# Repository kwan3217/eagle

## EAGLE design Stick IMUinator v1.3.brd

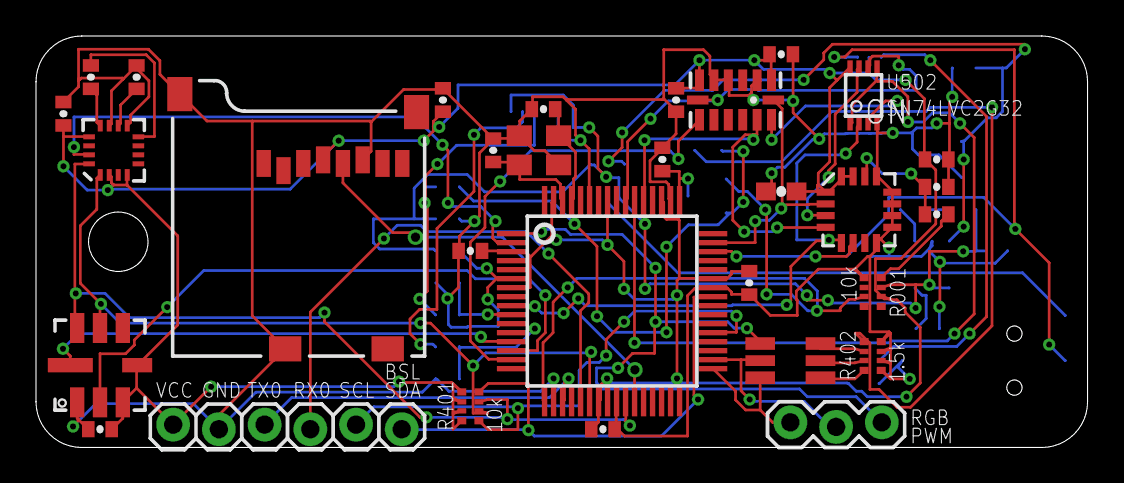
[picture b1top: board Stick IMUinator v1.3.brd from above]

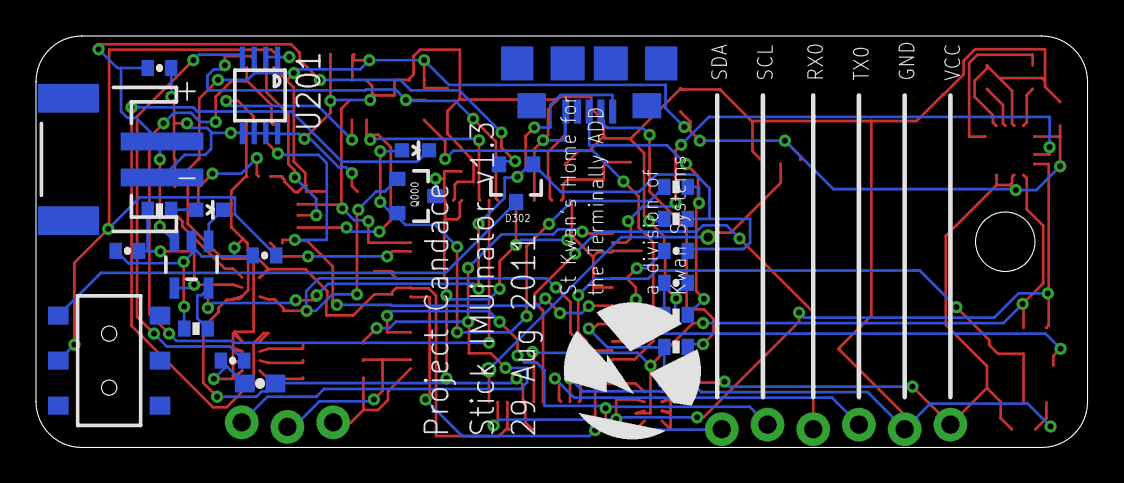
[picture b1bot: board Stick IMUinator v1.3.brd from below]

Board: 2 copper layers, 58.4 x 22.9 mm, 55 parts (23 on the bottom side), 53 nets.

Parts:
C010, C020, C461, C462: 22pF; 0402-CAP
C030, C101, C407, C423, C443, C451, C501, C601, C701, C802: 100nF; 0402-CAP
C201: 4.7uF; 0603-CAP
C203: 470pF; 0402-CAP
C204: 1uF; 0402-CAP
C301, C302, C606, C810: 4.7uF; 0402-CAP
C502: 10uF; 0603-CAP
C503: 10nF; 0402-CAP
C504: 470nF; 0402-CAP
C808: 220nF; 0402-CAP
D000, D301: RED; LED-0603
D302: PMEG2005CT; SOT-23-3
D401: GM5WA94310A
J301: JST 2mm; JST-2-SMD
J401: M06; 1X06_LOCK
J402: M03; 1X03_LOCK
JP1: STAND-OFF
Q000: PFET; SOT23-3
R001, R401: 10k; CRA04
R010, R020: 33; 0402-RES
R011, R302: 1.5k; 0402-RES
R031: 100k; 0402-RES
R301: 2.2k; 0402-RES
R402: 1.5k; CRA04
S201: SPST; AYZ0202
U101: BMP085
U201: 5219; MSOP08
U301: 73831; SOT23-5
U401: LPC2148; SQFP-S-10X10-64
U501: L3G4200D; LGA16-4X4
U502: SN74LVC2G32; DCU_8
U601: ADXL345; LGA14
U701: USD-SOCKETNEW; MICRO-SD-SOCKET-PP
U801: 5883; 16LPCC
U$1: USB_MICROB_JST; UB-MC5BR3-SD204-4S
Y401: TSX-3225; CRYSTAL_SMD

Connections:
ACCINT: U401.15, U601.8
AMOSI1: U502.3, U601.13
COMPINT: U401.2, U801.15
CONN_D+: R010.2, R011.2, U$1.3
CONN_D-: R020.2, U$1.2
CS0: U401.31, U701.2
CSA: U401.55, U502.6, U601.7
CSG: U401.9, U501.5, U502.2
EOC: U101.2, U401.14
GMOSI1: U501.3, U502.7
GND: C010.2, C020.2, C030.2, C101.2, C201.2, C203.2, C204.2, C301.2, C302.2, C407.2, C423.2, C443.2, C451.2, C461.1, C462.1, C501.2, C502.2, C503.2, C601.2, C606.2, C701.2, C802.2, C810.2, J301.1, J401.2, R001.1, R031.1, R301.1, R402.1, R402.2, R402.3, R402.4, U101.1, U201.5, U201.6, U201.7, U201.8, U301.2, U401.6, U401.18, U401.25, U401.42, U401.50, U401.59, U501.8, U501.9, U501.10, U501.11, U501.12, U501.13, U502.4, U601.2, U601.4, U601.5, U701.6, U701.CD2, U701.GND1, U801.9, U801.11, U$1.5, U$1.P$6, U$1.P$7, U$1.P$8, U$1.P$9, U$1.P$10, U$1.P$11, Y401.2, Y401.4
GYROINT: U401.46, U501.6
MISO0: U401.29, U701.7
MISO1: U401.53, U501.4, U601.12
MOSI0: U401.30, U701.3
MOSI1: U401.54, U502.1, U502.5
unnamed: C504.2, R001.8
unnamed: R301.2, U301.5
unnamed: D301.C, U301.1
unnamed: D301.A, R302.1
unnamed: D000.A, Q000.2, R011.1
unnamed: D000.C, R402.5
unnamed: D401.5, R402.7
unnamed: D401.6, R402.6
unnamed: D401.4, R402.8
unnamed: C808.1, U801.8
unnamed: C808.2, U801.12
unnamed: C810.1, U801.10
unnamed: C203.1, U201.4
unnamed: C503.1, C504.1, U501.14
PWMB: D401.1, J402.3, U401.1
PWMG: D401.3, J402.1, U401.33
PWMR: D401.2, J402.2, U401.34
RAW: C204.1, S201.2, U201.1, U201.2
RX0: J401.4, U401.21
SCK0: U401.27, U701.5
SCK1: U401.47, U501.2, U601.14
SCL0: R401.2, U101.6, U401.22, U801.1
SCL1: J401.5, R401.1, U401.37
SDA0: R401.3, U101.7, U401.26, U801.16
SDA1: J401.6, R401.4, U401.41
TX0: J401.3, U401.19
USBD+: C010.1, R010.1, U401.10
USBD-: C020.1, R020.1, U401.11
USB_LIGHT: Q000.1, R001.3, U401.17
USB_ON: R001.2, U401.58
VBUS: C030.1, C302.1, D302.1, R001.7, R031.2, R302.2, U301.4, U$1.1
VCC: C101.1, C201.1, C407.1, C423.1, C443.1, C451.1, C501.1, C502.1, C601.1, C606.1, C701.1, C802.1, J401.1, Q000.3, R001.6, R401.5, R401.6, R401.7, R401.8, U101.3, U101.4, U201.3, U401.3, U401.7, U401.23, U401.43, U401.49, U401.51, U401.57, U401.63, U501.1, U501.15, U501.16, U502.8, U601.1, U601.6, U701.4, U801.2, U801.4, U801.13
VIN: D302.3, S201.3
VLIPO: C301.1, D302.2, J301.2, U301.3
XCLR: U101.8, U401.13
XTAL1: C462.2, U401.62, Y401.1
XTAL2: C461.2, U401.61, Y401.3

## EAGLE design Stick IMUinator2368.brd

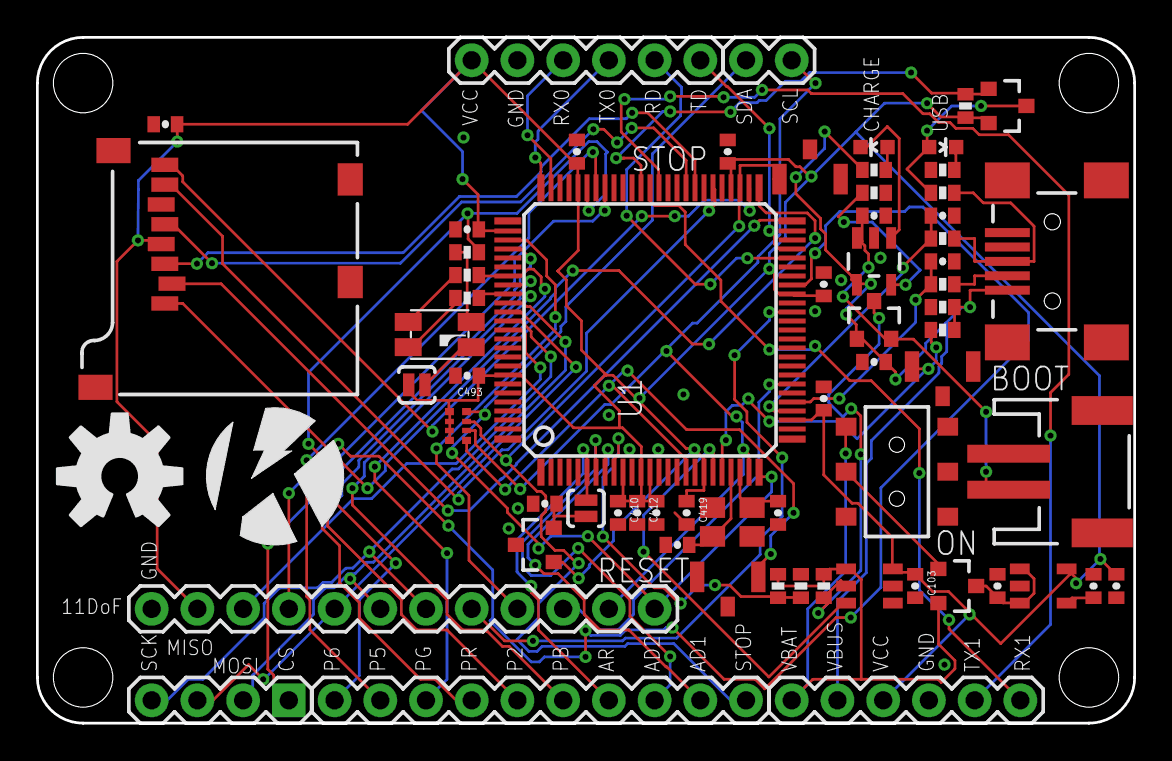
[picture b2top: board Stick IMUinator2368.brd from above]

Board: 2 copper layers, 61.0 x 38.1 mm, 71 parts (0 on the bottom side), 63 nets.

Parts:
C020, C030, C422, C423: 18pF; 0402-CAP
C103, C201: 1uF; 0402-CAP
C204, C410, C412, C413, C419, C428, C442, C454, C471, C477, C493, C701: 100nF; 0402-CAP
C205, C301, C302, C406: 4.7uF; 0402-CAP
D050, D301: RED; LED-0603
D302: DCC; SOT-23-3
D401: RGB; HSMF-C118
J001: USBSMD; USB-MINIB
J002: M01PTH; 1X02
J301: JST 2mm; JST-2-SMD
J401, J404: M06; 1X06
J402: M04; 1X04
J403: M10; 1X10
J406: M12PTH; 1X12
J701: USD-SOCKETNEW; MICRO-SD-SOCKET-PP
JP1, JP2, JP3, JP4: STAND-OFF
Q050, Q201: PMOS; SOT23-3
R010, R051, R301: 10k; 0402-RES
R011, R101, R102: 100k; 0402-RES
R020, R030, R482, R494: 33; 0402-RES
R031, R050, R302: 1.5k; 0402-RES
R103: 0.047; 0402-RES
R401: 10k; CRA04
R470: 150; 0402-RES
S010, S417, S453: SPST; B3U-1100P
S201: SPDT; AYZ0202
S401, S406: SOLDERJUMPERNO; SJ_2S-NO
U1: LPC2368; LQFP100
U101: 100V/V; SOT-23-6
U201: 5319; SOT-23-5
U301: 73831; SOT23-5
U402: 1525; SOT-23-3
U$1: KWAN_CIRCLE
U$2: OSHW-LOGO-L
Y401: 12M; CRYSTAL_SMD

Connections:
AD1: J403.9, U1.8
AD2: J403.8, U1.7
ADREF+: C406.1, S406.1, U402.2
ADREF-: J403.7, S406.2, U1.6
BATLVL: R101.2, R102.1, U1.9
BSL/STOP: J403.10, R401.7, S453.P$2, U1.53
CLK: J701.5, U1.59
CMD: J701.3, U1.58
CONN_D+: J001.D+, R030.2, R031.2
CONN_D-: J001.D-, R020.2
CS: J402.1, U1.79
CSA: J406.10, U1.88
CSG: J406.4, U1.78
CURRENT: U1.20, U101.6
DAT0: J701.7, U1.56
DAT1: J701.8, U1.52
DAT2: J701.1, U1.51
DAT3: J701.2, U1.50
DB: D401.4, R494.1
DG: D401.3, R482.1
DR: D401.2, R470.1
GND: C020.2, C030.2, C103.2, C201.2, C204.2, C205.2, C301.2, C302.2, C406.2, C410.2, C412.2, C413.2, C419.2, C422.1, C423.1, C428.2, C442.2, C454.2, C471.2, C477.2, C493.2, C701.2, J001.GND, J301.1, J401.5, J404.4, J406.12, J701.6, J701.CD2, J701.GND1, J701.GND3, R011.1, R050.2, R101.1, R301.1, S010.P$2, S010.P$3, S201.1, S417.P$1, S417.P$3, S453.P$1, S453.P$3, U1.11, U1.15, U1.31, U1.41, U1.55, U1.72, U1.76, U1.92, U101.1, U101.2, U201.2, U301.2, U402.3, Y401.2, Y401.4
IA: J406.9, U1.43
IC: J406.3, U1.32
IG: J406.5, U1.40
MISO: J402.3, J406.8, U1.86
MOSI: J402.2, J406.7, U1.85
unnamed: D301.A, R302.1
unnamed: R301.2, U301.5
unnamed: D301.C, U301.1
unnamed: D050.A, Q050.3, R031.1
unnamed: D050.C, R050.1
unnamed: Q201.1, S201.2
unnamed: C204.1, U201.4
PWM2: J403.5, U1.83
PWM5: J403.2, U1.69
PWM6: J403.1, U1.68
PWMB: J403.6, R494.2, U1.84
PWMG: J403.3, R482.2, U1.82
PWMR: J403.4, R470.2, U1.70
RAW: C201.1, Q201.3, U201.1, U201.3
RD: J401.2, U1.46
RGB_Q: D401.1, S401.1
RST: R401.5, S417.P$2, U1.17
RXD0: J401.4, U1.74
RXD1: J404.6, U1.63
SCK: J402.4, J406.6, U1.87
SCL: J002.1, J406.2, R401.6, U1.24
SDA: J002.2, J406.1, R401.8, U1.25
TD: J401.1, U1.47
TXD0: J401.3, U1.75
TXD1: J404.5, U1.62
USBD+: C030.1, R030.1, U1.29
USBD-: C020.1, R020.1, U1.30
USB_ON: R010.1, S010.P$1, U1.21
USB_SOFTCONNECT: Q050.1, R051.2, U1.64
VBUS: C302.1, D302.1, J001.VBUS, J404.2, R010.2, R011.2, R302.2, U301.4
VCC: C103.1, C205.1, C410.1, C412.1, C413.1, C419.1, C428.1, C442.1, C454.1, C471.1, C477.1, C493.1, C701.1, J401.6, J404.3, J406.11, J701.4, Q050.2, R051.1, R401.1, R401.2, R401.3, R401.4, S401.2, U1.10, U1.12, U1.13, U1.19, U1.28, U1.42, U1.54, U1.71, U1.77, U1.93, U101.3, U201.5, U402.1
VIN+: D302.3, R103.1, U101.5
VIN-: J404.1, Q201.2, R102.2, R103.2, S201.3, U101.4
VLIPO: C301.1, D302.2, J301.2, U301.3
XTAL1: C422.2, U1.22, Y401.3
XTAL2: C423.2, U1.23, Y401.1

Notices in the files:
Stick IMUinator2368.brd:
Released under the Creative Commons Attribution Share-Alike 3.0 License
http://creativecommons.org/licenses/by-sa/3.0
